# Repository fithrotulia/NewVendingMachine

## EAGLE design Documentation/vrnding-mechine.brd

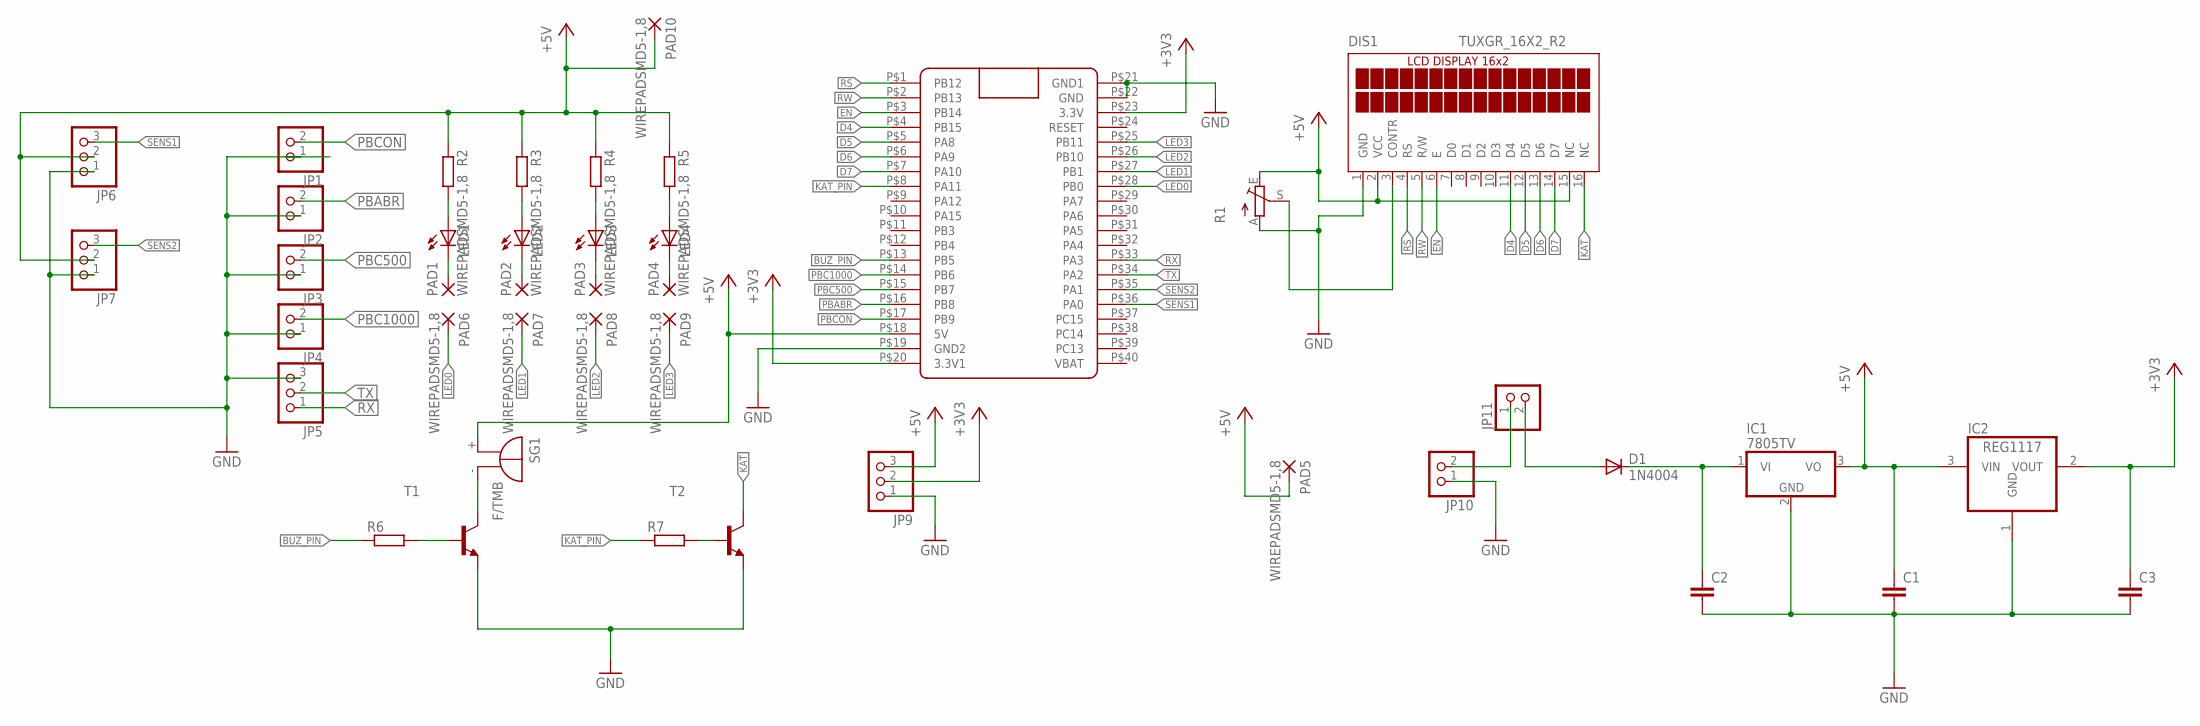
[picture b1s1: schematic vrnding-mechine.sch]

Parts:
C1, C2, C3: C-EU025-030X050; C025-030X050
D1: 1N4004; DO41-10
DIS1: TUXGR_16X2_R2
IC1: 7805TV; TO220V
IC2: REG1117; SOT223
JP1, JP2, JP3, JP4, JP10, JP11: PINHD-1X2; 1X02
JP5, JP6, JP7, JP9: PINHD-1X3; 1X03
LED1, LED2, LED3, LED4: LED5MM
PAD1, PAD2, PAD3, PAD4, PAD5, PAD6, PAD7, PAD8, PAD9, PAD10: WIREPADSMD5-1,8; 5-1,8
R1: TRIM_EU-CA6V; CA6V
R2, R3, R4, R5, R6, R7: R-EU_0309/10; 0309/10
SG1: F/TMB
T1, T2: -NPN-TO92-ECB; TO92-ECB
U$1: BLUE_PILL

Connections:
+3V3: C3.1, IC2.2 (VOUT), JP9.2, U$1.P$20 (3.3V1), U$1.P$23 (3.3V)
+5V: C1.1, DIS1.2 (VCC), DIS1.15 (NC), IC1.3 (VO), IC2.3 (VIN), JP6.2, JP7.2, JP9.3, PAD5.1, PAD10.1, R1.E, R2.1, R3.1, R4.1, R5.1, SG1.+, U$1.P$18 (5V)
BUZ_PIN: R6.1, U$1.P$13 (PB5)
D4: DIS1.11 (D4), U$1.P$4 (PB15)
D5: DIS1.12 (D5), U$1.P$5 (PA8)
D6: DIS1.13 (D6), U$1.P$6 (PA9)
D7: DIS1.14 (D7), U$1.P$7 (PA10)
EN: DIS1.6 (E), U$1.P$3 (PB14)
GND: C1.2, C2.2, C3.2, DIS1.1 (GND), IC1.2 (GND), IC2.1 (GND), JP1.1, JP2.1, JP3.1, JP4.1, JP5.3, JP6.1, JP7.1, JP9.1, JP10.1, R1.A, T1.E, T2.E, U$1.P$19 (GND2), U$1.P$21 (GND1), U$1.P$22 (GND)
KAT: DIS1.16 (NC), T2.C
KAT_PIN: R7.1, U$1.P$8 (PA11)
LED0: PAD6.1, U$1.P$28 (PB0)
LED1: PAD7.1, U$1.P$27 (PB1)
LED2: PAD8.1, U$1.P$26 (PB10)
LED3: PAD9.1, U$1.P$25 (PB11)
unnamed: DIS1.3 (CONTR), R1.S
unnamed: SG1.-, T1.C
unnamed: R6.2, T1.B
unnamed: LED1.A, R2.2
unnamed: LED2.A, R3.2
unnamed: LED3.A, R4.2
unnamed: LED4.A, R5.2
unnamed: R7.2, T2.B
unnamed: LED2.K (C), PAD2.1
unnamed: LED1.K (C), PAD1.1
unnamed: LED3.K (C), PAD3.1
unnamed: LED4.K (C), PAD4.1
unnamed: JP10.2, JP11.1
unnamed: D1.A, JP11.2
unnamed: C2.1, D1.C, IC1.1 (VI)
PBABR: JP2.2, U$1.P$16 (PB8)
PBC500: JP3.2, U$1.P$15 (PB7)
PBC1000: JP4.2, U$1.P$14 (PB6)
PBCON: JP1.2, U$1.P$17 (PB9)
RS: DIS1.4 (RS), U$1.P$1 (PB12)
RW: DIS1.5 (R/W), U$1.P$2 (PB13)
RX: JP5.1, U$1.P$33 (PA3)
SENS1: JP6.3, U$1.P$36 (PA0)
SENS2: JP7.3, U$1.P$35 (PA1)
TX: JP5.2, U$1.P$34 (PA2)

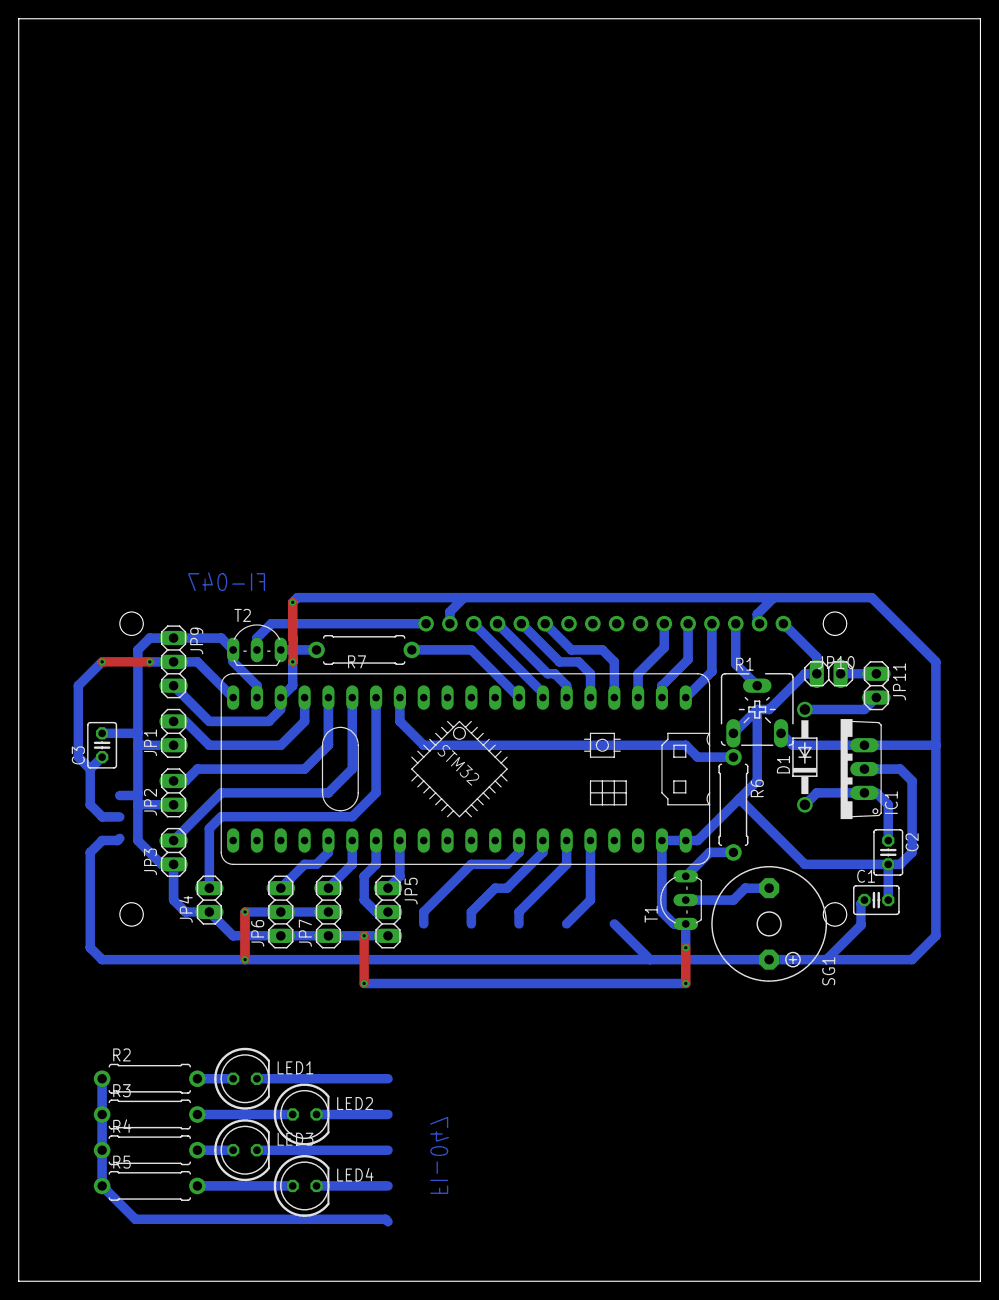
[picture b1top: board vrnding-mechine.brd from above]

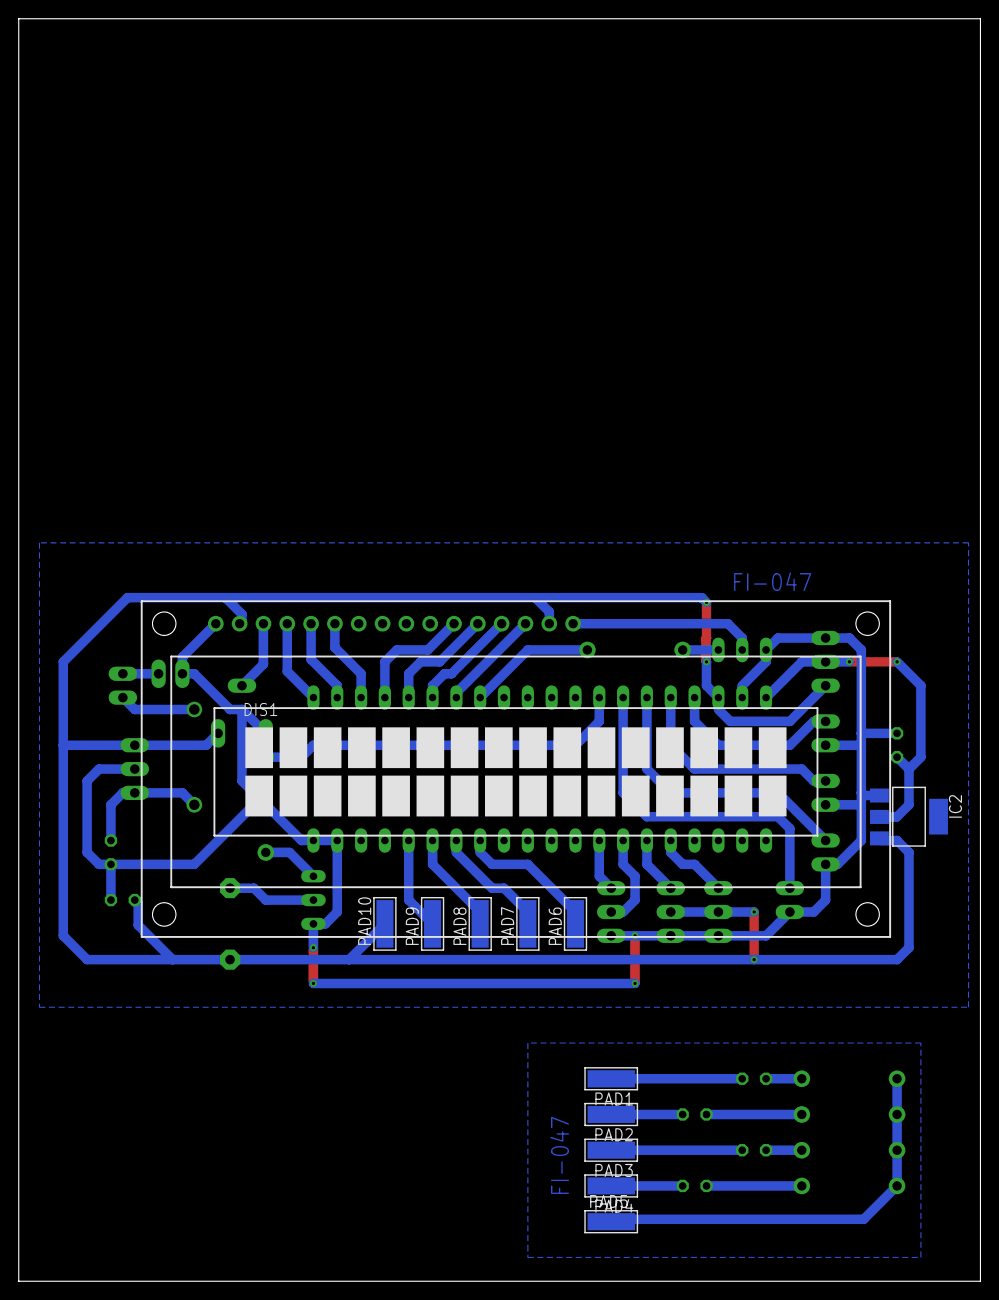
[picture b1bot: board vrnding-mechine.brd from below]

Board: 2 copper layers, 102.5 x 134.6 mm, 42 parts (12 on the bottom side), 40 nets.

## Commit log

2019-12-01 membuat projek vending machine sederhana
